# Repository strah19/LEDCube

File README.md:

# LEDCube

Directions for PCB!!!

All the needed files have been generated by me already. These files are located under `cube/gerber.zip`. There are many different
companies that can make the PCB. You are welcome to choose whatever one you would like. They will all accept the generated files so
that should not be a concern. I suggest JLCPCB because of the low cost however it is from China so it may take some time to deliver. 
For this PCB they quoted me at $12 for 5 boards. I have also used them before with good results. On whatever website you choose, you'll 
just have to add the gerber files and all the settings should be good to go. Nothing on our part has to be done. Below is a screenshot 
of what the PCB will look like. Let me know if there is something you want changed and I will before you buy it. Thanks!

### Notes
- You will have to buy IC sockets for the chips.
- The resisitors for the LED's, NOT the ones connected to transistor base pin, should all be between 220 and 330 ohms.
- For the arduino, please use female header pins and then pop the arduino in. This way the arduino can be easily taken out.
- To the left of the arduino, there is a header. These are connected to the arduinos analog pins and are there so they are available for use (possibly a button).
- Also to the left of the arduino there is a place for a capacitor. The capacitor is there to protected it from noise. IMPORTANT: if you are using a polarized capacitor,
  meaning one side is supposed to be positive and the other negative, the right hole is the negative and the left hole is the positive. Usually, the capacitor legs will be
  different lengths, the longer one is positive and the shorter one is negative. I suggest this capacitor be valued around 10 - 100 uF, whatever you have.
- The pinout of the transistors is VERY important. I'm not sure what transistors you have but this is the following pin out they need to have (check the datasheet): 1: emitter, 2:base,
  and 3: collector. This can also be seen in the schematic (pdf). These transisitors are PN2222A's. If you have these great, otherwise just check the datasheet of the ones you have and if
  they have the same pinout they can work. Also, make sure they are oriented the correct way when placing them on the board (the emitter is directly connected to ground, this can be verified    with a multimeter).
- Lastly, on top of each chip, there is a place for a capacitor. Please use ceramic capacitor that is NOT polarized and has a value of 0.1 uF. These are also filter capacitors.

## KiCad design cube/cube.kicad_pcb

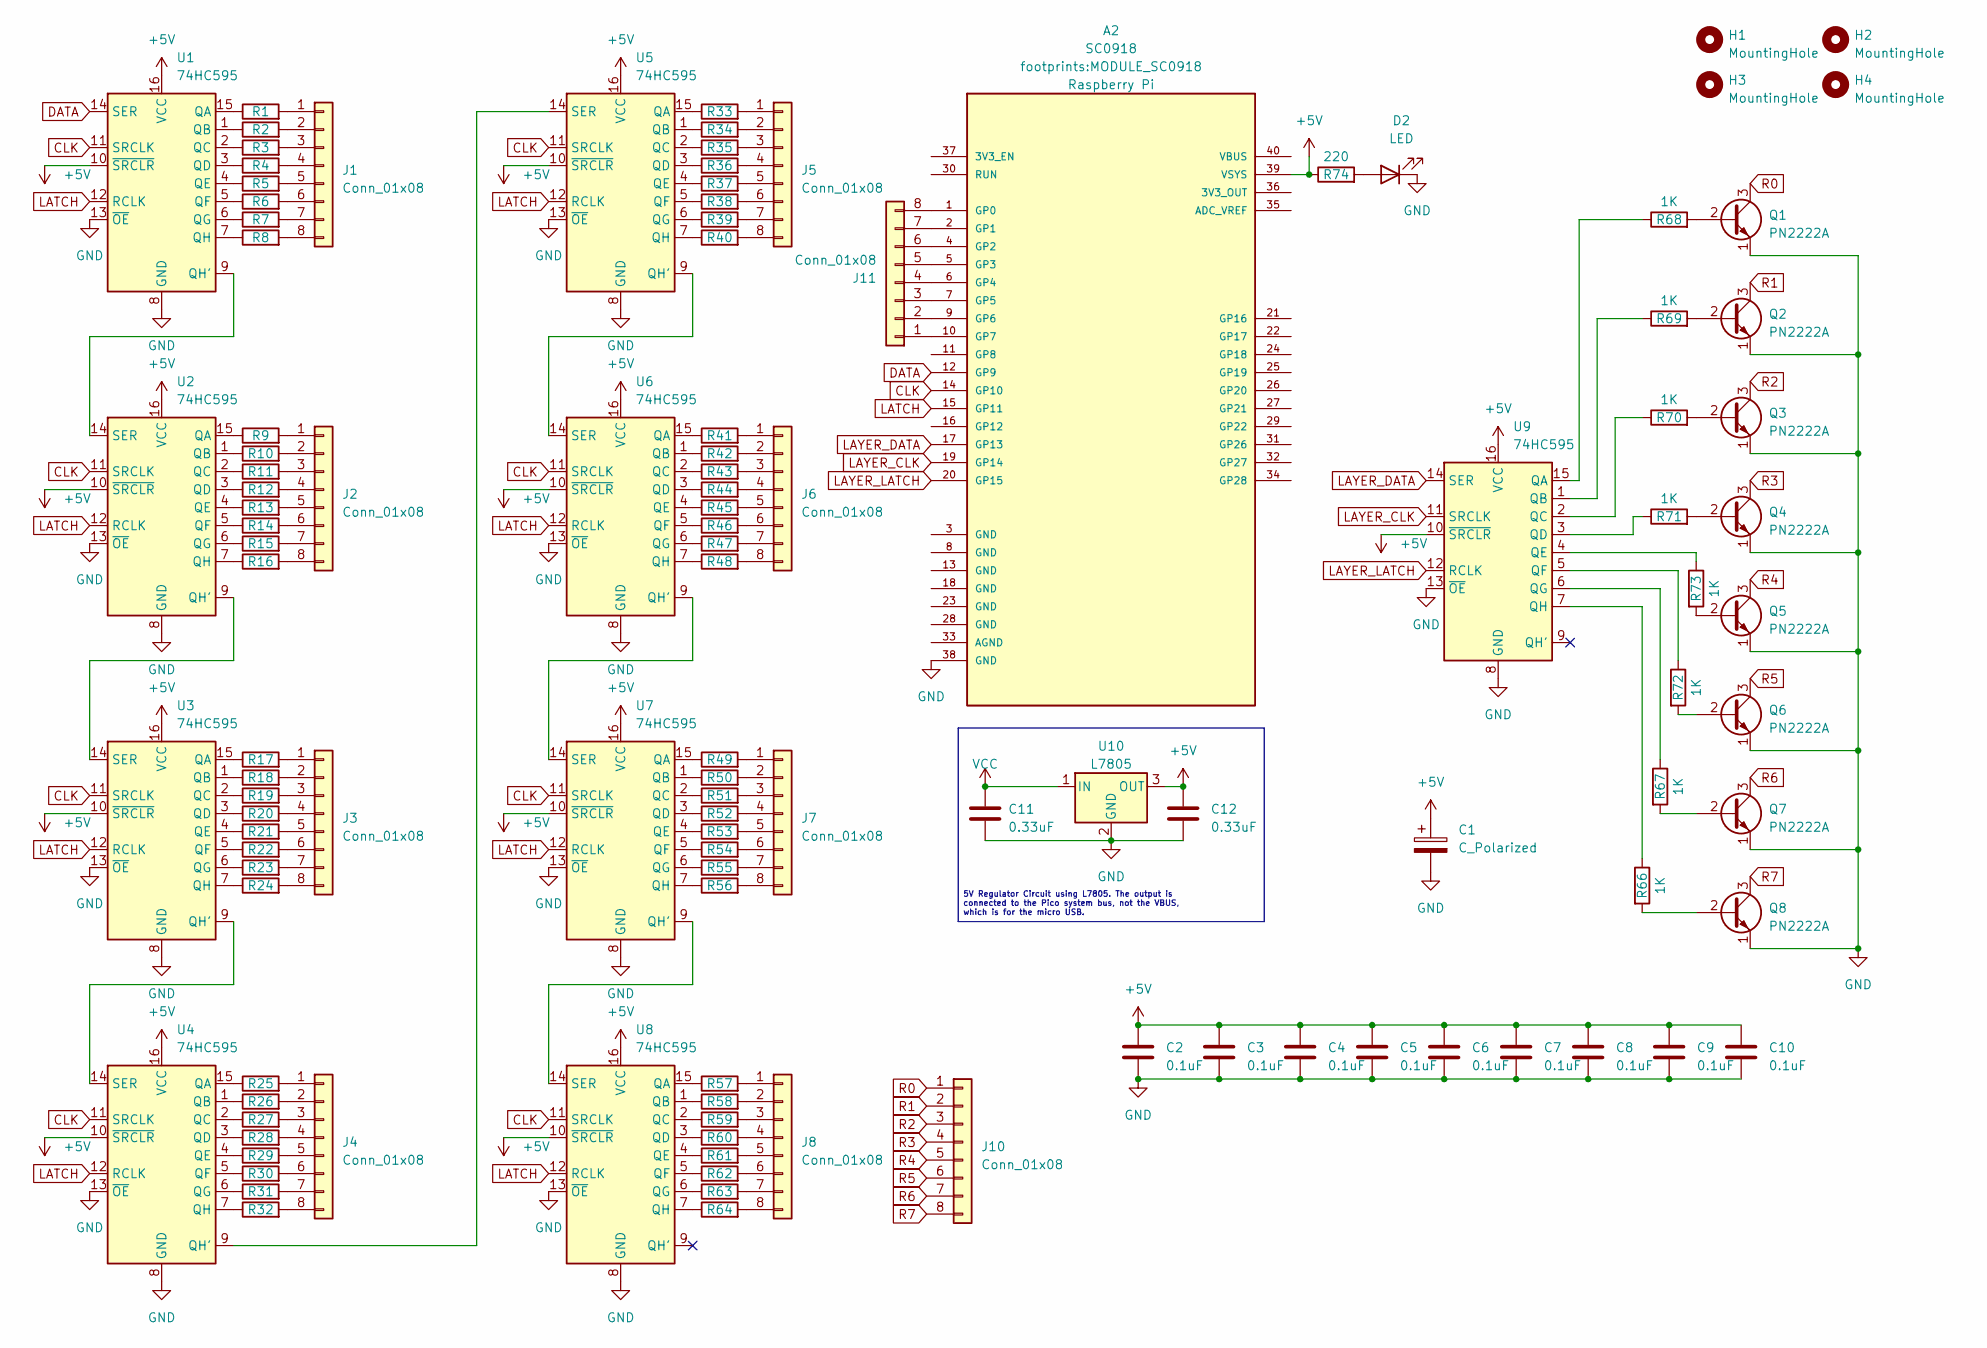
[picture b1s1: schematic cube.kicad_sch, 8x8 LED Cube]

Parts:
A2: SC0918; MODULE_SC0918; PARTREV 1.6
C1: C_Polarized; C_Radial_D10.0mm_H20.0mm_P5.00mm
C2, C3, C4, C5, C6, C7, C8, C9, C10: 0.1uF; C_Disc_D5.1mm_W3.2mm_P5.00mm
C11, C12: 0.33uF; C_Disc_D5.1mm_W3.2mm_P5.00mm
D2: LED; LED_D5.0mm_Clear
H1, H2, H3, H4: MountingHole; MountingHole_3.2mm_M3_DIN965_Pad
J1, J2, J3, J4, J5, J6, J7, J8, J10, J11: Conn_01x08; PinHeader_1x08_P2.54mm_Vertical
Q1, Q2, Q3, Q4, Q5, Q6, Q7, Q8: PN2222A; TO-92_Inline
R1, R2, R3, R4, R5, R6, R7, R8, R9, R10, R11, R12, R13, R14, R15, R16, R17, R18, R19, R20, R21, R22, R23, R24, R25, R26, R27, R28, R29, R30, R31, R32, R33, R34, R35, R36, R37, R38, R39, R40, R41, R42, R43, R44, R45, R46, R47, R48, R49, R50, R51, R52, R53, R54, R55, R56, R57, R58, R59, R60, R61, R62, R63, R64: R; R_Axial_DIN0207_L6.3mm_D2.5mm_P10.16mm_Horizontal
R66, R67, R68, R69, R70, R71, R72, R73: 1K; R_Axial_DIN0207_L6.3mm_D2.5mm_P10.16mm_Horizontal
R74: 220; R_Axial_DIN0207_L6.3mm_D2.5mm_P10.16mm_Horizontal
U1, U2, U3, U4, U5, U6, U7, U8, U9: 74HC595; DIP-16_W7.62mm_Socket
U10: L7805; TO-220-3_Vertical

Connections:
+5V: A2.39 (VSYS), C1.1, C2.1, C3.1, C4.1, C5.1, C6.1, C7.1, C8.1, C9.1, C10.1, C12.1, R74.1, U1.10 (~SRCLR), U1.16 (VCC), U2.10 (~SRCLR), U2.16 (VCC), U3.10 (~SRCLR), U3.16 (VCC), U4.10 (~SRCLR), U4.16 (VCC), U5.10 (~SRCLR), U5.16 (VCC), U6.10 (~SRCLR), U6.16 (VCC), U7.10 (~SRCLR), U7.16 (VCC), U8.10 (~SRCLR), U8.16 (VCC), U9.10 (~SRCLR), U9.16 (VCC), U10.3 (OUT)
CLK: A2.14 (GP10), U1.11 (SRCLK), U2.11 (SRCLK), U3.11 (SRCLK), U4.11 (SRCLK), U5.11 (SRCLK), U6.11 (SRCLK), U7.11 (SRCLK), U8.11 (SRCLK)
DATA: A2.12 (GP9), U1.14 (SER)
GND: A2.38 (GND), C1.2, C2.2, C3.2, C4.2, C5.2, C6.2, C7.2, C8.2, C9.2, C10.2, C11.2, C12.2, D2.1 (K), Q1.1 (E), Q2.1 (E), Q3.1 (E), Q4.1 (E), Q5.1 (E), Q6.1 (E), Q7.1 (E), Q8.1 (E), U1.8 (GND), U1.13 (~OE), U2.8 (GND), U2.13 (~OE), U3.8 (GND), U3.13 (~OE), U4.8 (GND), U4.13 (~OE), U5.8 (GND), U5.13 (~OE), U6.8 (GND), U6.13 (~OE), U7.8 (GND), U7.13 (~OE), U8.8 (GND), U8.13 (~OE), U9.8 (GND), U9.13 (~OE), U10.2 (GND)
LATCH: A2.15 (GP11), U1.12 (RCLK), U2.12 (RCLK), U3.12 (RCLK), U4.12 (RCLK), U5.12 (RCLK), U6.12 (RCLK), U7.12 (RCLK), U8.12 (RCLK)
LAYER_CLK: A2.19 (GP14), U9.11 (SRCLK)
LAYER_DATA: A2.17 (GP13), U9.14 (SER)
LAYER_LATCH: A2.20 (GP15), U9.12 (RCLK)
unnamed: A2.1 (GP0), J11.8
unnamed: A2.2 (GP1), J11.7
unnamed: A2.4 (GP2), J11.6
unnamed: A2.5 (GP3), J11.5
unnamed: A2.6 (GP4), J11.4
unnamed: A2.7 (GP5), J11.3
unnamed: A2.9 (GP6), J11.2
unnamed: A2.10 (GP7), J11.1
unnamed: D2.2 (A), R74.2
unnamed: J1.1, R1.2
unnamed: J1.2, R2.2
unnamed: J1.3, R3.2
unnamed: J1.4, R4.2
unnamed: J1.5, R5.2
unnamed: J1.6, R6.2
unnamed: J1.7, R7.2
unnamed: J1.8, R8.2
unnamed: J2.1, R9.2
unnamed: J2.2, R10.2
unnamed: J2.3, R11.2
unnamed: J2.4, R12.2
unnamed: J2.5, R13.2
unnamed: J2.6, R14.2
unnamed: J2.7, R15.2
unnamed: J2.8, R16.2
unnamed: J3.1, R17.2
unnamed: J3.2, R18.2
unnamed: J3.3, R19.2
unnamed: J3.4, R20.2
unnamed: J3.5, R21.2
unnamed: J3.6, R22.2
unnamed: J3.7, R23.2
unnamed: J3.8, R24.2
unnamed: J4.1, R25.2
unnamed: J4.2, R26.2
unnamed: J4.3, R27.2
unnamed: J4.4, R28.2
unnamed: J4.5, R29.2
unnamed: J4.6, R30.2
unnamed: J4.7, R31.2
unnamed: J4.8, R32.2
unnamed: J5.1, R33.2
unnamed: J5.2, R34.2
unnamed: J5.3, R35.2
unnamed: J5.4, R36.2
unnamed: J5.5, R37.2
unnamed: J5.6, R38.2
unnamed: J5.7, R39.2
unnamed: J5.8, R40.2
unnamed: J6.1, R41.2
unnamed: J6.2, R42.2
unnamed: J6.3, R43.2
unnamed: J6.4, R44.2
unnamed: J6.5, R45.2
unnamed: J6.6, R46.2
unnamed: J6.7, R47.2
unnamed: J6.8, R48.2
unnamed: J7.1, R49.2
unnamed: J7.2, R50.2
unnamed: J7.3, R51.2
unnamed: J7.4, R52.2
unnamed: J7.5, R53.2
unnamed: J7.6, R54.2
unnamed: J7.7, R55.2
unnamed: J7.8, R56.2
unnamed: J8.1, R57.2
unnamed: J8.2, R58.2
unnamed: J8.3, R59.2
unnamed: J8.4, R60.2
unnamed: J8.5, R61.2
unnamed: J8.6, R62.2
unnamed: J8.7, R63.2
unnamed: J8.8, R64.2
unnamed: Q1.2 (B), R68.2
unnamed: Q2.2 (B), R69.2
unnamed: Q3.2 (B), R70.2
unnamed: Q4.2 (B), R71.2
unnamed: Q5.2 (B), R73.2
unnamed: Q6.2 (B), R72.2
unnamed: Q7.2 (B), R67.2
unnamed: Q8.2 (B), R66.2
unnamed: R1.1, U1.15 (QA)
unnamed: R2.1, U1.1 (QB)
unnamed: R3.1, U1.2 (QC)
unnamed: R4.1, U1.3 (QD)
unnamed: R5.1, U1.4 (QE)
unnamed: R6.1, U1.5 (QF)
unnamed: R7.1, U1.6 (QG)
unnamed: U1.9 (QH'), U2.14 (SER)
unnamed: R8.1, U1.7 (QH)
unnamed: R9.1, U2.15 (QA)
unnamed: R10.1, U2.1 (QB)
unnamed: R11.1, U2.2 (QC)
unnamed: R12.1, U2.3 (QD)
unnamed: R13.1, U2.4 (QE)
unnamed: R14.1, U2.5 (QF)
unnamed: R15.1, U2.6 (QG)
unnamed: U2.9 (QH'), U3.14 (SER)
unnamed: R16.1, U2.7 (QH)
unnamed: R17.1, U3.15 (QA)
unnamed: R18.1, U3.1 (QB)
unnamed: R19.1, U3.2 (QC)
unnamed: R20.1, U3.3 (QD)
unnamed: R21.1, U3.4 (QE)
unnamed: R22.1, U3.5 (QF)
unnamed: R23.1, U3.6 (QG)
unnamed: U3.9 (QH'), U4.14 (SER)
unnamed: R24.1, U3.7 (QH)
unnamed: R25.1, U4.15 (QA)
unnamed: R26.1, U4.1 (QB)
unnamed: R27.1, U4.2 (QC)
unnamed: R28.1, U4.3 (QD)
unnamed: R29.1, U4.4 (QE)
unnamed: R30.1, U4.5 (QF)
unnamed: R31.1, U4.6 (QG)
unnamed: U4.9 (QH'), U5.14 (SER)
unnamed: R32.1, U4.7 (QH)
unnamed: R33.1, U5.15 (QA)
unnamed: R34.1, U5.1 (QB)
unnamed: R35.1, U5.2 (QC)
unnamed: R36.1, U5.3 (QD)
unnamed: R37.1, U5.4 (QE)
unnamed: R38.1, U5.5 (QF)
unnamed: R39.1, U5.6 (QG)
unnamed: U5.9 (QH'), U6.14 (SER)
unnamed: R40.1, U5.7 (QH)
unnamed: R41.1, U6.15 (QA)
unnamed: R42.1, U6.1 (QB)
unnamed: R43.1, U6.2 (QC)
unnamed: R44.1, U6.3 (QD)
unnamed: R45.1, U6.4 (QE)
unnamed: R46.1, U6.5 (QF)
unnamed: R47.1, U6.6 (QG)
unnamed: U6.9 (QH'), U7.14 (SER)
unnamed: R48.1, U6.7 (QH)
unnamed: R49.1, U7.15 (QA)
unnamed: R50.1, U7.1 (QB)
unnamed: R51.1, U7.2 (QC)
unnamed: R52.1, U7.3 (QD)
unnamed: R53.1, U7.4 (QE)
unnamed: R54.1, U7.5 (QF)
unnamed: R55.1, U7.6 (QG)
unnamed: U7.9 (QH'), U8.14 (SER)
unnamed: R56.1, U7.7 (QH)
unnamed: R57.1, U8.15 (QA)
unnamed: R58.1, U8.1 (QB)
unnamed: R59.1, U8.2 (QC)
unnamed: R60.1, U8.3 (QD)
unnamed: R61.1, U8.4 (QE)
unnamed: R62.1, U8.5 (QF)
unnamed: R63.1, U8.6 (QG)
unnamed: R64.1, U8.7 (QH)
unnamed: R68.1, U9.15 (QA)
unnamed: R69.1, U9.1 (QB)
unnamed: R70.1, U9.2 (QC)
unnamed: R71.1, U9.3 (QD)
unnamed: R73.1, U9.4 (QE)
unnamed: R72.1, U9.5 (QF)
unnamed: R67.1, U9.6 (QG)
unnamed: R66.1, U9.7 (QH)
R0: J10.1, Q1.3 (C)
R1: J10.2, Q2.3 (C)
R2: J10.3, Q3.3 (C)
R3: J10.4, Q4.3 (C)
R4: J10.5, Q5.3 (C)
R5: J10.6, Q6.3 (C)
R6: J10.7, Q7.3 (C)
R7: J10.8, Q8.3 (C)
VCC: C11.1, U10.1 (IN)

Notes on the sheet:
5V Regulator Circuit using L7805. The output is connected to the Pico system bus, not the VBUS, which is for the micro USB.

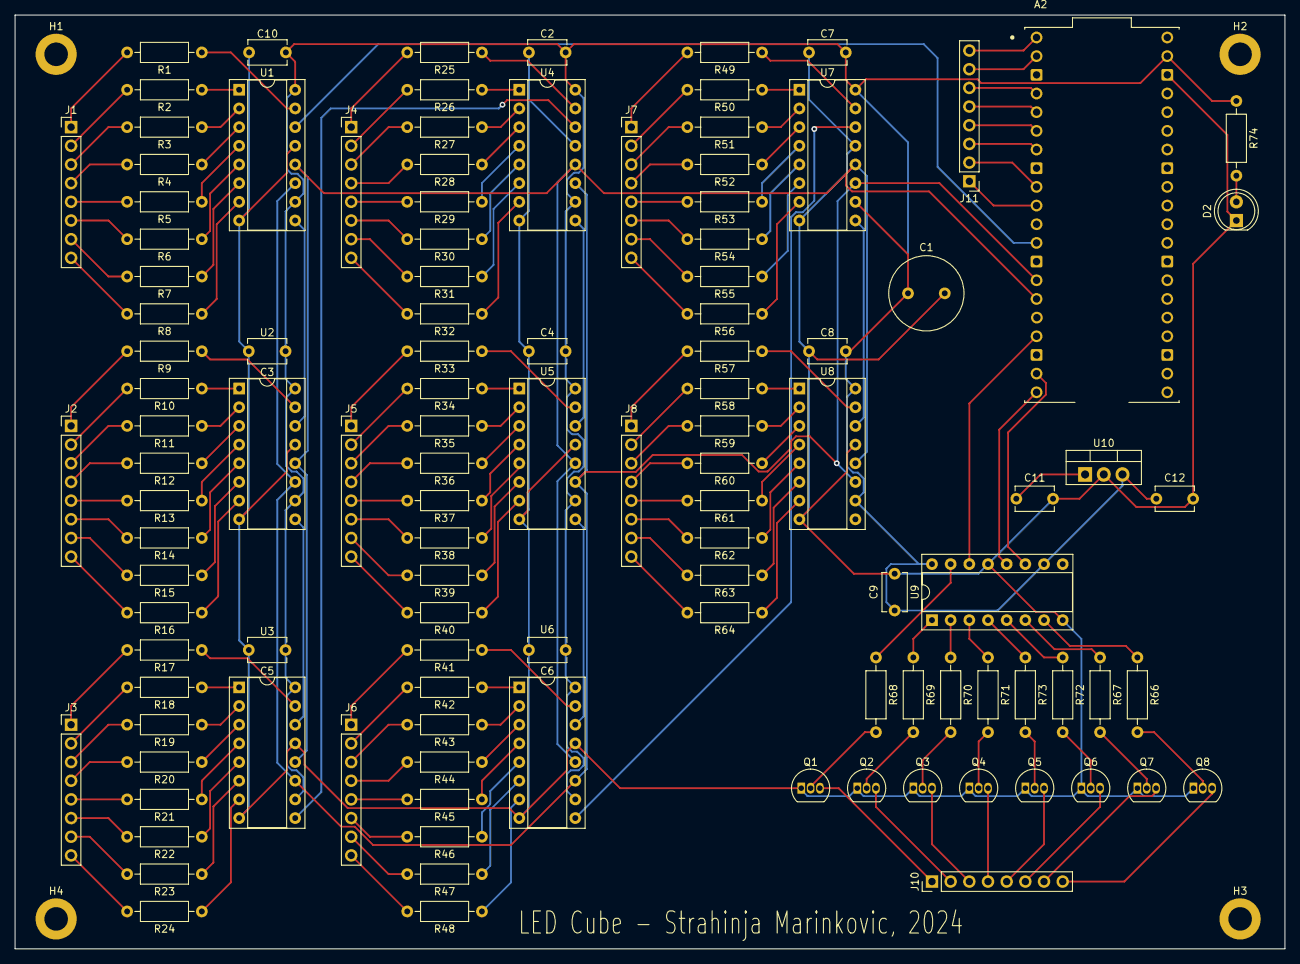
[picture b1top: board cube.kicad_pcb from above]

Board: 2 copper layers, 172.7 x 127.0 mm, 119 parts (0 on the bottom side), 177 nets.

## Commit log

2023-03-14 added schematics
2023-07-19 created pcb
2023-07-19 updated pcb.
2023-07-19 updated pcb_image
2023-07-19 updated pcb image
2024-05-25 updated gerber files.
